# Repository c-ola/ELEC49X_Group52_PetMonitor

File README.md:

Repo for ELEC 49X group 52

## ADXL345 Accelerometer

*Sensor Library:* https://github.com/adafruit/Adafruit_ADXL345/tree/master

*Data Sheet:* https://www.analog.com/media/en/technical-documentation/data-sheets/adxl345.pdf

## GPS
https://registry.platformio.org/libraries/mikalhart/TinyGPSPlus

## Deep Sleep
Guide to using it: https://randomnerdtutorials.com/esp32-deep-sleep-arduino-ide-wake-up-sources/

## MAX17043
https://www.analog.com/media/en/technical-documentation/data-sheets/MAX17043-MAX17044.pdf

## Battery Circuit
https://emariete.com/en/co2-meter-with-battery-well-done/

## BLE
https://randomnerdtutorials.com/esp32-web-bluetooth/

## LoRa
https://cdn.sparkfun.com/assets/learn_tutorials/8/0/4/RFM95_96_97_98W.pdf

## Maybe for the app?
https://registry.platformio.org/libraries/bblanchon/ArduinoJson

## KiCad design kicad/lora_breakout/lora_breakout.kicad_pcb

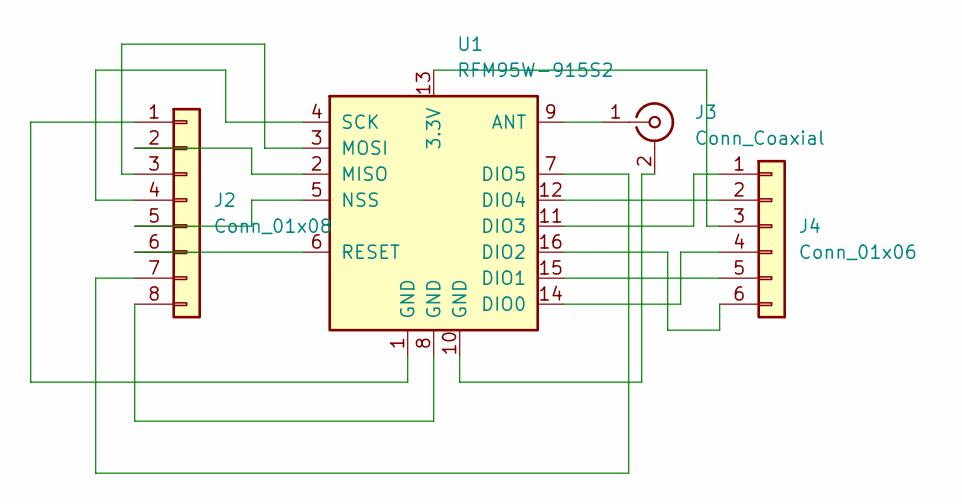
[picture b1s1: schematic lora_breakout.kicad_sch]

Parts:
J2: Conn_01x08; PinHeader_1x08_P2.54mm_Vertical
J3: Conn_Coaxial; SMA_Amphenol_901-144_Vertical
J4: Conn_01x06; PinHeader_1x06_P2.54mm_Vertical; Part Number 1-0601FBV0T
U1: RFM95W-915S2; HOPERF_RFM9XW_SMD

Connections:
unnamed: J2.1, U1.1 (GND)
unnamed: J2.2, U1.2 (MISO)
unnamed: J2.3, U1.3 (MOSI)
unnamed: J2.4, U1.4 (SCK)
unnamed: J2.5, U1.5 (NSS)
unnamed: J2.6, U1.6 (RESET)
unnamed: J2.7, U1.7 (DIO5)
unnamed: J2.8, U1.8 (GND)
unnamed: J3.2 (Ext), U1.10 (GND)
unnamed: J3.1 (In), U1.9 (ANT)
unnamed: J4.1, U1.11 (DIO3)
unnamed: J4.2, U1.12 (DIO4)
unnamed: J4.3, U1.13 (3.3V)
unnamed: J4.4, U1.14 (DIO0)
unnamed: J4.5, U1.15 (DIO1)
unnamed: J4.6, U1.16 (DIO2)

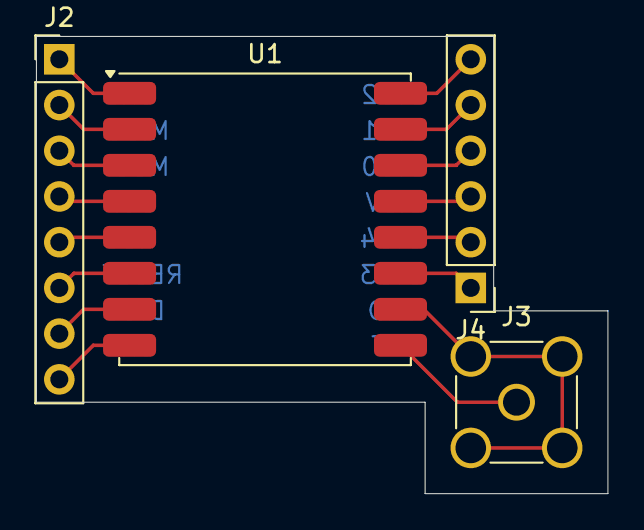
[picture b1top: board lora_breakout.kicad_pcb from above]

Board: 2 copper layers, 31.8 x 25.4 mm, 4 parts (0 on the bottom side), 16 nets.

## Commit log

2024-10-25 blinks light based on acceleration
2024-10-28 added support for multiple main files
2024-10-30 Update platformio.ini
    added batteryTest environment
2024-10-30 updated things
2024-10-30 Added LoRa functionality to sender
2024-10-30 add gps2 test
2024-10-31 added esp32c3
2024-10-31 Added GPS to sender
2024-10-31 add c3 stuff
2024-11-05 Added gps packet sending
2024-11-07 Update platformio.ini
    add library for battery max17043
2024-11-08 Added deep sleep
2024-11-08 Added fuel gauge to sender
2024-11-08 hello
2024-11-08 Receivers displays % on screen
2024-11-08 screen updates on time
2024-11-14 added pinout
2024-11-28 updated lora breakout
